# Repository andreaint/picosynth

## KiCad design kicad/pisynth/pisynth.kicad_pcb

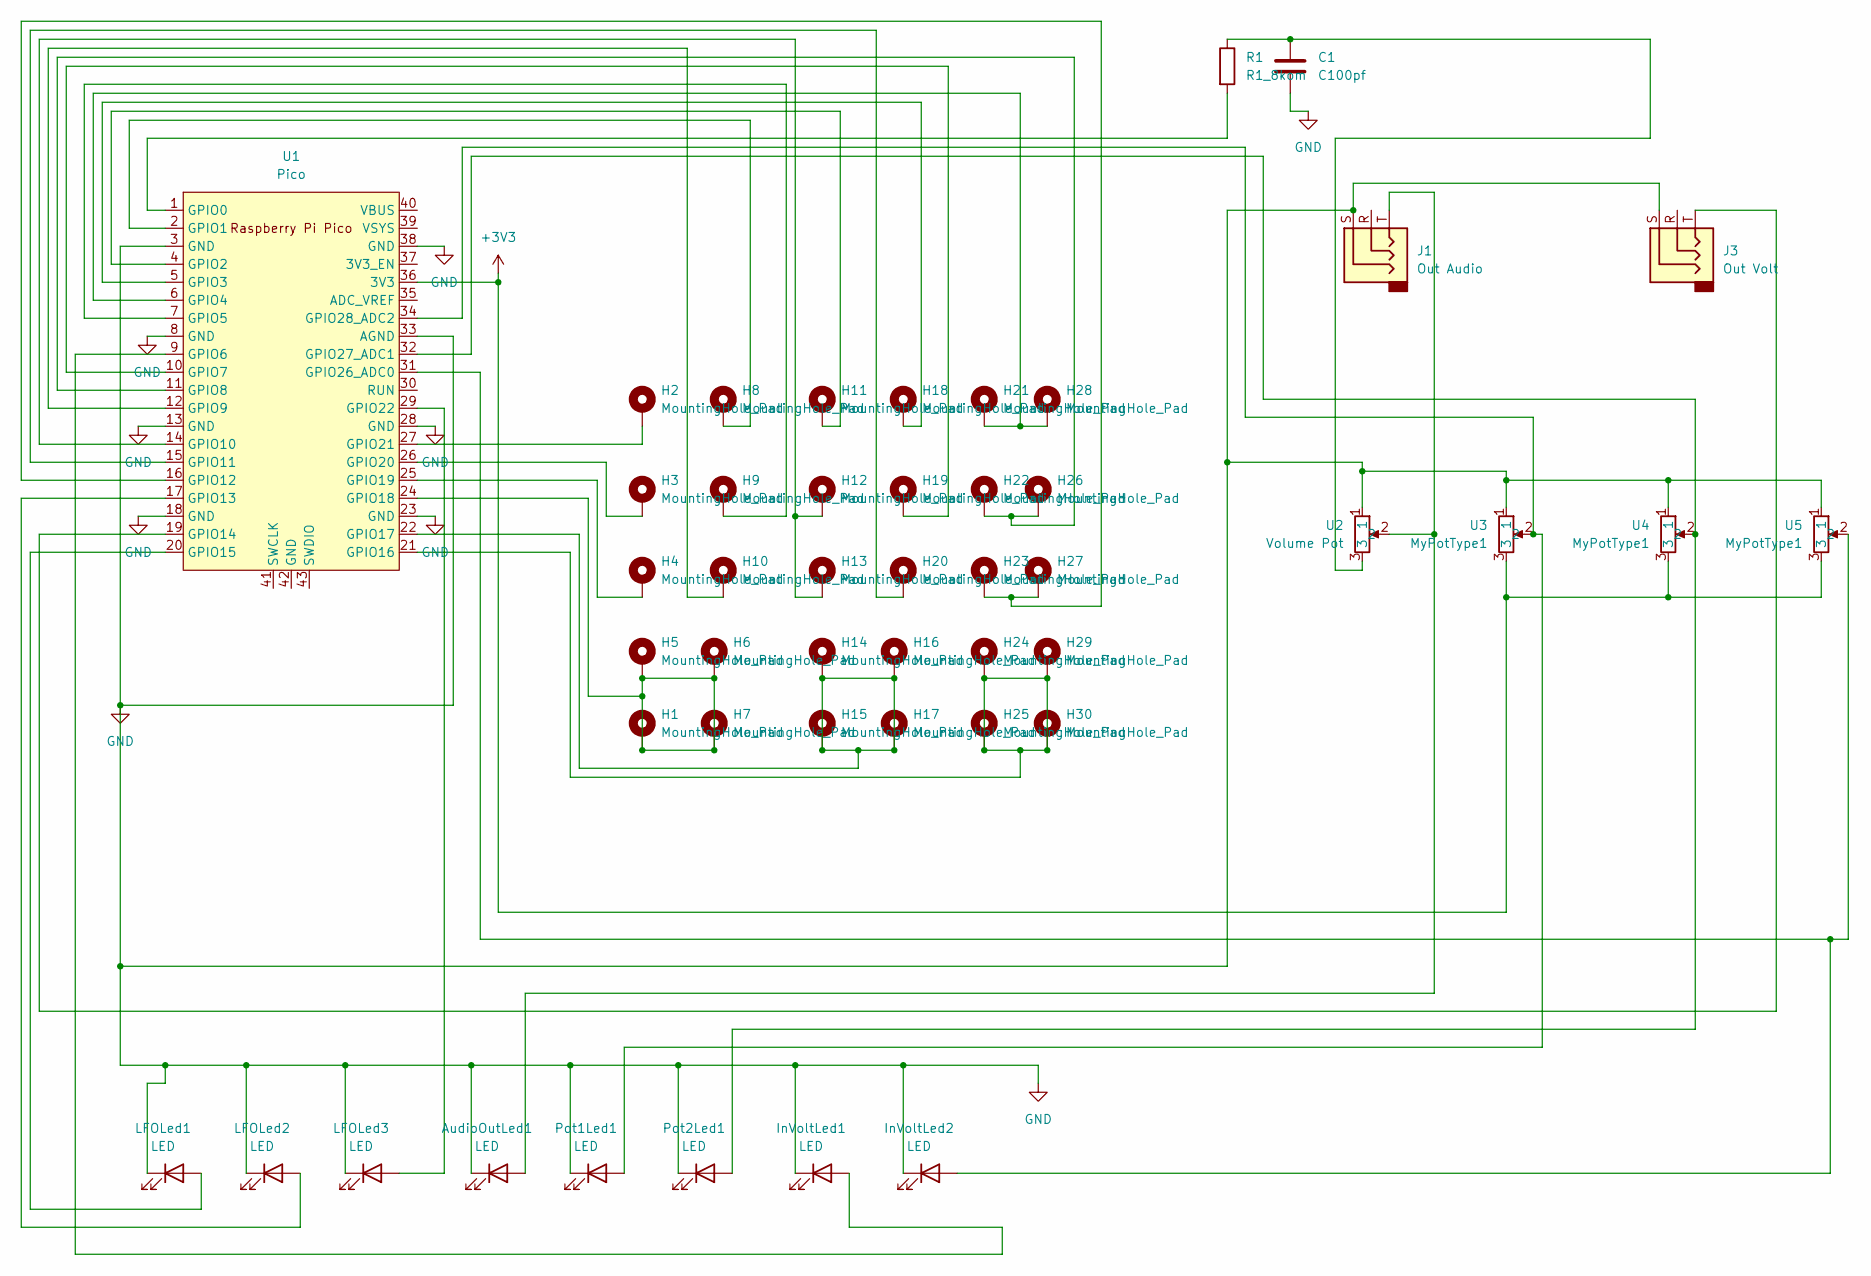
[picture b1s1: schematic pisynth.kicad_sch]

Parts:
AudioOutLed1: LED; myLed
C1: C100pf; myCapacitor
H1, H2, H3, H4, H5, H6, H7, H8, H9, H10, H11, H12, H13, H14, H15, H16, H17, H18, H19, H20, H21, H22, H23, H24, H25, H26, H27, H28, H29, H30: MountingHole_Pad; myPad
InVoltLed1, InVoltLed2: LED; myLed
J1: Out Audio; myAudioJackFootprint
J3: Out Volt; myAudioJackFootprint
LFOLed1, LFOLed2, LFOLed3: LED; myLed
Pot1Led1, Pot2Led1: LED; myLed
R1: R1_8kom; myResistor
U1: Pico; myPico
U2: Volume Pot; myDiscPot
U3, U4, U5: MyPotType1; myDiscPot

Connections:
+3V3: U1.36 (3V3), U3.3, U4.3, U5.3
GND: AudioOutLed1.1 (K), C1.2, InVoltLed1.1 (K), InVoltLed2.1 (K), J1.S, J3.S, LFOLed1.1 (K), LFOLed2.1 (K), LFOLed3.1 (K), Pot1Led1.1 (K), Pot2Led1.1 (K), U1.3 (GND), U1.8 (GND), U1.13 (GND), U1.18 (GND), U1.23 (GND), U1.28 (GND), U1.33 (AGND), U1.38 (GND), U2.1, U3.1, U4.1, U5.1
unnamed: AudioOutLed1.2 (A), J1.T, U2.2
unnamed: H1.1, H5.1, H6.1, H7.1, U1.24 (GPIO18)
unnamed: H2.1, U1.27 (GPIO21)
unnamed: H3.1, U1.26 (GPIO20)
unnamed: H4.1, U1.25 (GPIO19)
unnamed: H8.1, U1.2 (GPIO1)
unnamed: H9.1, U1.7 (GPIO5)
unnamed: H10.1, U1.12 (GPIO9)
unnamed: H11.1, U1.4 (GPIO2)
unnamed: H12.1, H13.1, U1.14 (GPIO10)
unnamed: H14.1, H15.1, H16.1, H17.1, U1.22 (GPIO17)
unnamed: H18.1, U1.5 (GPIO3)
unnamed: H19.1, U1.10 (GPIO7)
unnamed: H20.1, U1.15 (GPIO11)
unnamed: H21.1, H28.1, U1.6 (GPIO4)
unnamed: H22.1, H26.1, U1.11 (GPIO8)
unnamed: H23.1, H27.1, U1.16 (GPIO12)
unnamed: H24.1, H25.1, H29.1, H30.1, U1.21 (GPIO16)
unnamed: InVoltLed1.2 (A), U1.9 (GPIO6)
unnamed: InVoltLed2.2 (A), U1.31 (GPIO26_ADC0), U5.2
unnamed: J3.T, U1.19 (GPIO14)
unnamed: LFOLed1.2 (A), U1.20 (GPIO15)
unnamed: LFOLed2.2 (A), U1.17 (GPIO13)
unnamed: LFOLed3.2 (A), U1.29 (GPIO22)
unnamed: Pot1Led1.2 (A), U1.34 (GPIO28_ADC2), U3.2
unnamed: Pot2Led1.2 (A), U1.32 (GPIO27_ADC1), U4.2
unnamed: R1.2, U1.1 (GPIO0)
unnamed: C1.1, R1.1, U2.3

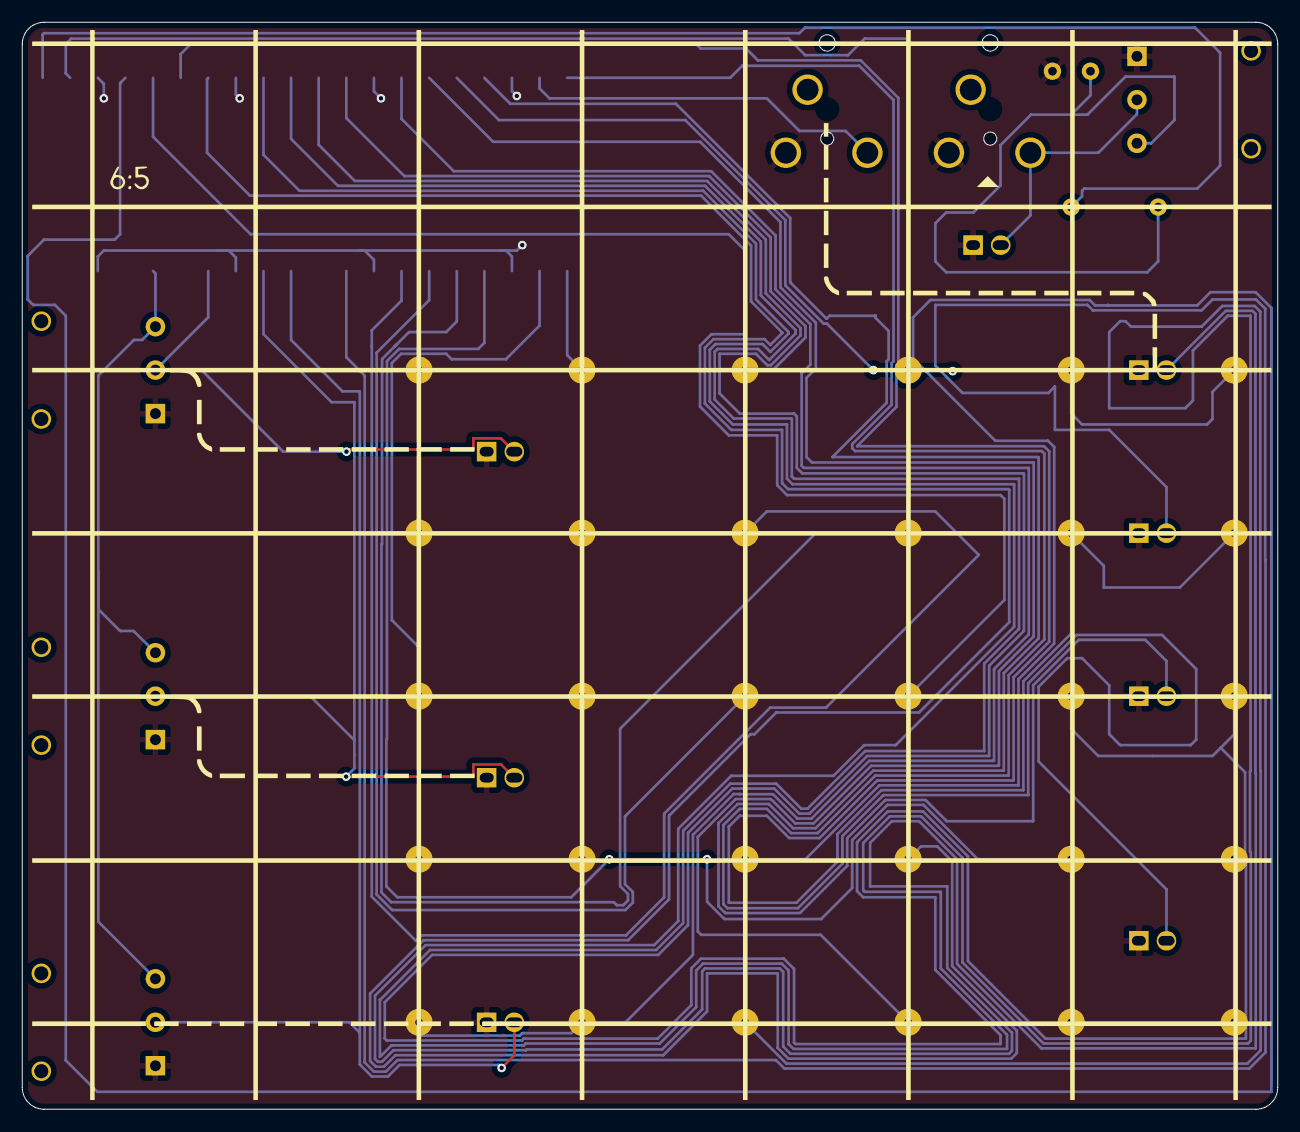
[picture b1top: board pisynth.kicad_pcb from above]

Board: 2 copper layers, 115.5 x 100.0 mm, 47 parts (1 on the bottom side), 30 nets.

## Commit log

2023-07-07 progress
